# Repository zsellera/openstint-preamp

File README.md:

# OpenStint Loop Preamplifier Board

The **OpenStint Loop Preamplifier Board** is an optional front-end module, designed for the [OpenStint Laptimer System](https://github.com/zsellera/openstint). It provides signal conditioning and amplification for the parallel-wire "antenna", ensuring clean, stable, and maximized signal transfer to the timing receiver.

## 🔧 Features

- Fully compatible with the OpenStint timing receiver interface. Operated from the bias-tee available on HackRF One and RTLSDR.
- Output is matched to 50 Ohm.
- +12 dB gain low-noise amplifier
- Fits Hammond's 1590L-style aluminium cases
- Power pin available for 1S batteries (remove `L6` or `FB2` in this case, or add DC-block capacitor before the SDR).
- Open hardware design – schematics and PCB available under permissive license
- Directly manufacturable at JLCPCB (LCSC part codes provided).

## ✳️ Measurement Results

The following measurements were made at the `VNA_IN` port (after the balun).

**POWER GAIN**

**INPUT MATCHING**

## Schematics

## 🗺 Roadmap / Project ideas

Add an optional 75 Ohm output as well, or add a separate 50 to 50+75 splitter. This hardware change should have a software counterpart, which reads both the OpenStint and MyLaps decoders, and merges the results into a single stream for laptiming applications. We could keep both open and commercial transponders to co-exists on the same track this way. Also, upgrading post-4.4 firmware won't be such a headache neither.

Automatic gain control: even a simple one could increase the dynamic range of the decoders.

---
Part of the OpenStint Laptimer System – open, modular, and precise RC timing.

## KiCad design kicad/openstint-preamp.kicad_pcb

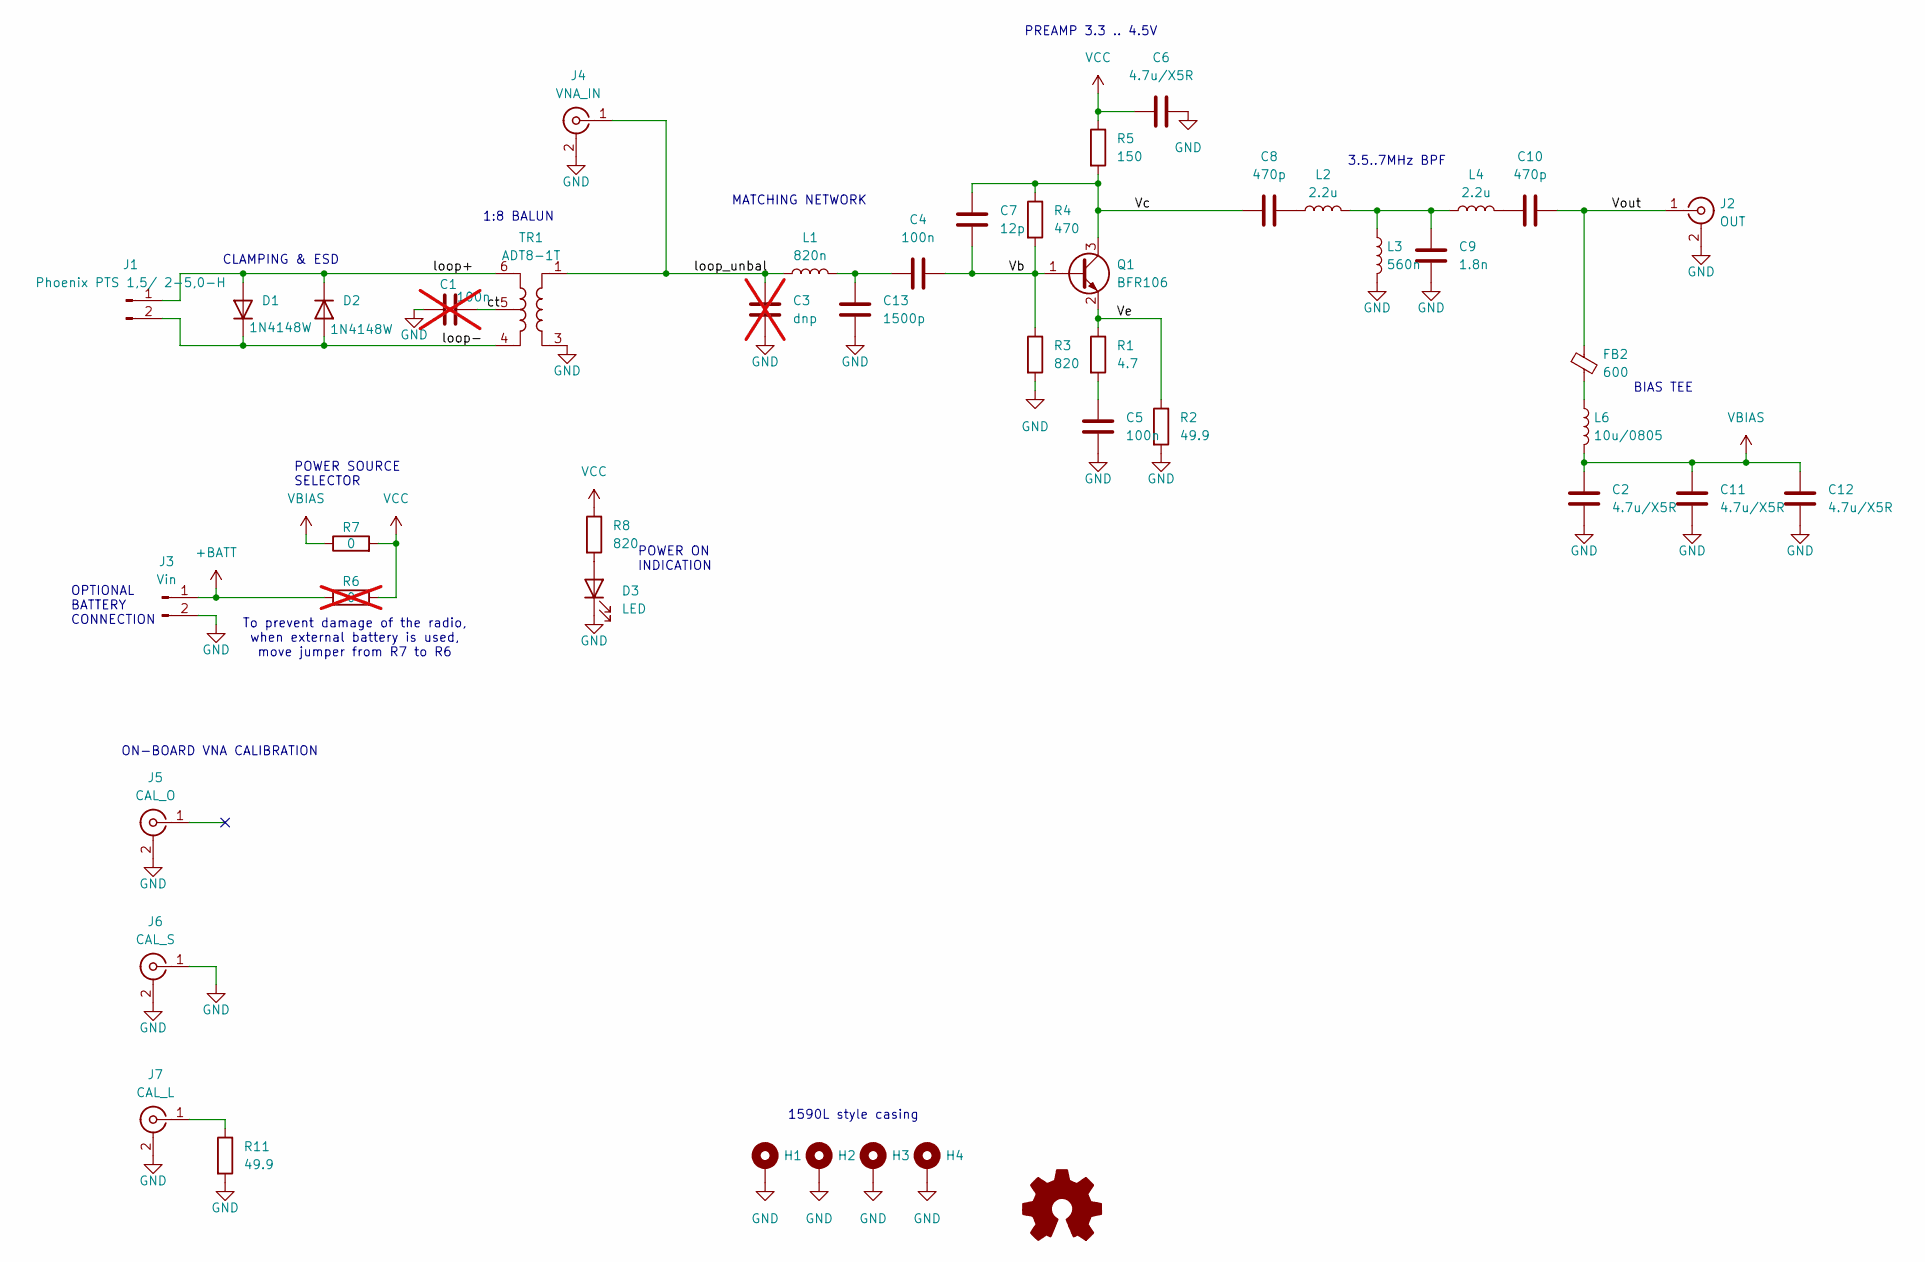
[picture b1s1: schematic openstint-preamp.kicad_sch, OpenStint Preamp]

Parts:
C1: 100n; C_0603_1608Metric; LCSC C14663; not fitted
C2, C6, C11, C12: 4.7u/X5R; C_0603_1608Metric; LCSC C19666
C3: dnp; C_0603_1608Metric; not fitted
C4, C5: 100n; C_0603_1608Metric; LCSC C14663
C7: 12p; C_0603_1608Metric; LCSC C38523
C8, C10: 470p; C_0603_1608Metric; LCSC C1620
C9: 1.8n; C_0603_1608Metric; LCSC C107042
C13: 1500p; C_0603_1608Metric; LCSC C1595
D1, D2: 1N4148W; D_SOD-123F; LCSC C81598
D3: LED; LED_1206_3216Metric_ReverseMount_Hole1.8x2.4mm; mouser 710-156120VS75000
FB2: 600; L_0805_2012Metric; LCSC C1017
H1, H2, H3, H4: MountingHole_Pad; MountingHole_4.3mm_M4_DIN965_Pad
J1: Phoenix PTS 1,5/ 2-5,0-H; TerminalBlock_Phoenix_PT-1,5-2-5.0-H_1x02_P5.00mm_Horizontal; mouser 651-1792863
J2: OUT; SMA_Amphenol_132134-16_Vertical
J3: Vin; JST_PH_B2B-PH-K_1x02_P2.00mm_Vertical; LCSC C131337
J4: VNA_IN; U.FL_Hirose_U.FL-R-SMT-1_Vertical; LCSC C5137195
J5: CAL_O; U.FL_Hirose_U.FL-R-SMT-1_Vertical; LCSC C5137195
J6: CAL_S; U.FL_Hirose_U.FL-R-SMT-1_Vertical; LCSC C5137195
J7: CAL_L; U.FL_Hirose_U.FL-R-SMT-1_Vertical; LCSC C5137195
L1: 820n; L_0603_1608Metric; LCSC C18213078
L2, L4: 2.2u; L_0603_1608Metric; LCSC C337910
L3: 560n; L_0603_1608Metric; LCSC C114773
L6: 10u/0805; L_0805_2012Metric; LCSC C88173
Q1: BFR106; SOT-23; LCSC C439780
R1: 4.7; R_0603_1608Metric; LCSC C23164
R2, R11: 49.9; R_0603_1608Metric; LCSC C23185
R3, R8: 820; R_0603_1608Metric; LCSC C23253
R4: 470; R_0603_1608Metric; LCSC C23179
R5: 150; R_0603_1608Metric; LCSC C22808
R6: 0; R_0603_1608Metric; LCSC C21189; not fitted
R7: 0; R_0603_1608Metric; LCSC C21189
SYM1: Logo_Open_Hardware_Small; OSHW-Logo2_9.8x8mm_SilkScreen
TR1: ADT8-1T; Mini-Circuits_CD637_H5.23mm

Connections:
+BATT: J3.1, R6.1
/Vb: C4.2, C7.1, Q1.1 (B), R3.1, R4.2
/Vc: C7.2, C8.1, Q1.3 (C), R4.1, R5.2
/Ve: Q1.2 (E), R1.1, R2.1
/Vout: C10.2, FB2.1, J2.1 (In)
/ct: C1.2, TR1.5
/loop+: D1.2 (A), D2.1 (K), J1.1, TR1.6
/loop-: D1.1 (K), D2.2 (A), J1.2, TR1.4
/loop_unbal: C3.1, J4.1 (In), L1.1, TR1.1
GND: C1.1, C2.1, C3.2, C5.2, C6.2, C9.2, C11.1, C12.1, C13.2, D3.1 (K), H1.1, H2.1, H3.1, H4.1, J2.2 (Ext), J3.2, J4.2 (Ext), J5.2 (Ext), J6.1 (In), J6.2 (Ext), J7.2 (Ext), L3.2, R2.2, R3.2, R11.2, TR1.3
unnamed: C5.1, R1.2
unnamed: C8.2, L2.1
unnamed: C9.1, L2.2, L3.1, L4.1
unnamed: C10.1, L4.2
unnamed: C4.1, C13.1, L1.2
unnamed: D3.2 (A), R8.2
unnamed: FB2.2, L6.1
unnamed: J7.1 (In), R11.1
VBIAS: C2.2, C11.2, C12.2, L6.2, R7.1
VCC: C6.1, R5.1, R6.2, R7.2, R8.1

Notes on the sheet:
POWER ON INDICATION
MATCHING NETWORK
OPTIONAL BATTERY CONNECTION
BIAS TEE
1590L style casing
ON-BOARD VNA CALIBRATION
PREAMP 3.3 .. 4.5V
1:8 BALUN
POWER SOURCE SELECTOR
CLAMPING & ESD
To prevent damage of the radio, when external battery is used, move jumper from R7 to R6
3.5..7MHz BPF

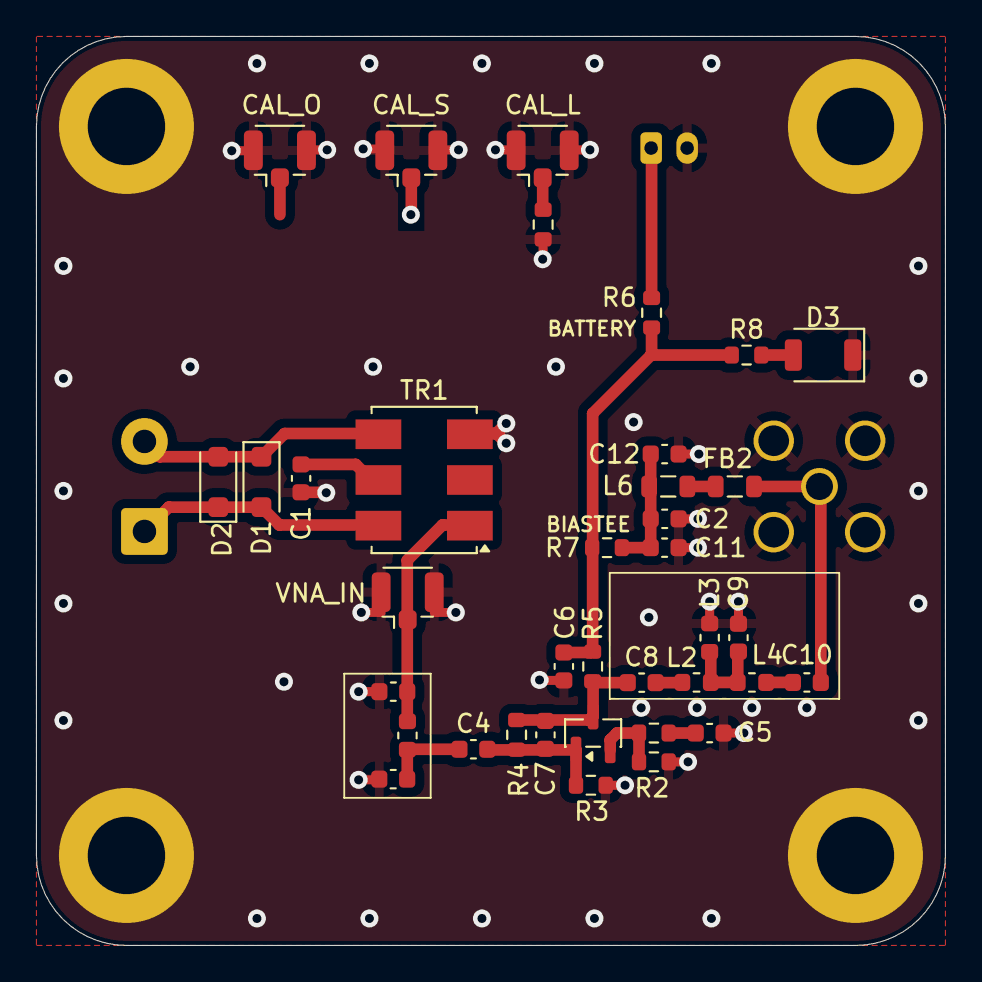
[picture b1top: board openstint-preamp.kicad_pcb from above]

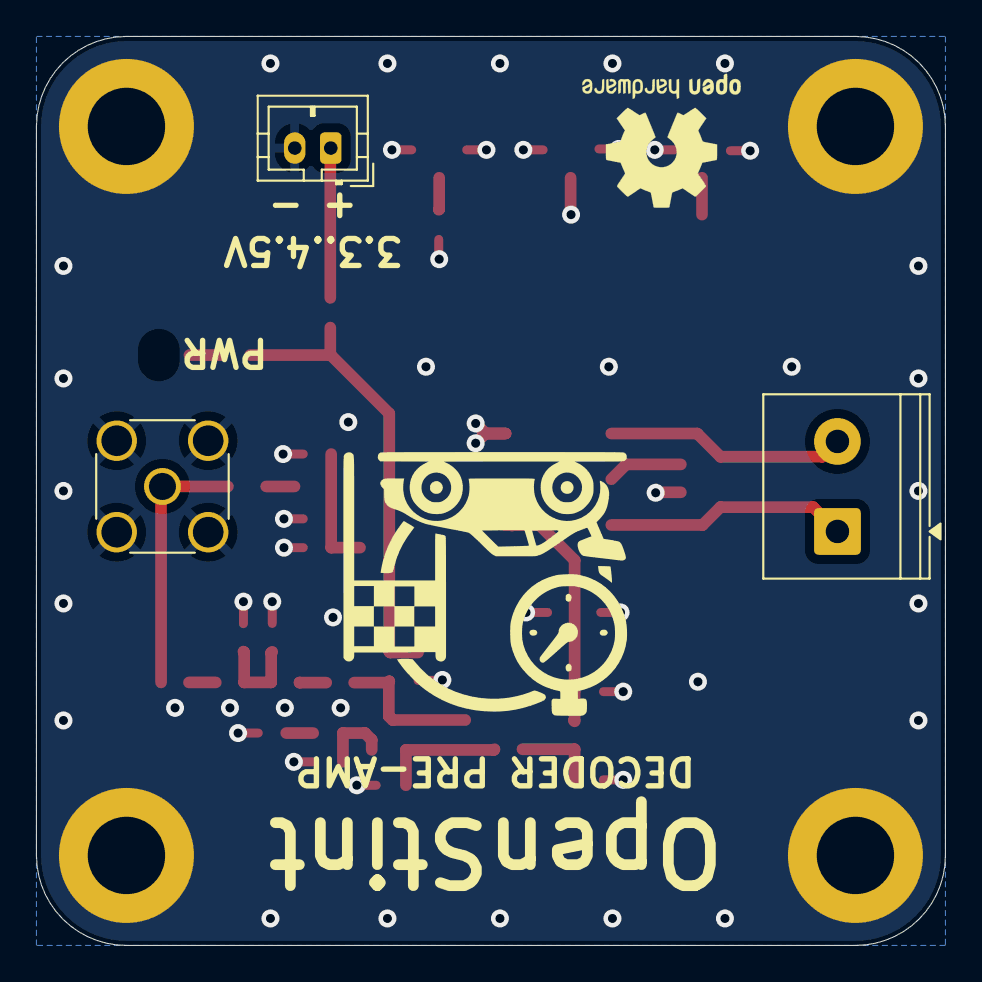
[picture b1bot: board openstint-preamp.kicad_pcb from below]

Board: 2 copper layers, 50.5 x 50.5 mm, 45 parts (4 on the bottom side), 20 nets.

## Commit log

2025-11-07 readme added
2025-11-07 Fix GitHub link and add schematics section
    Updated the GitHub link in the README and added a schematics section with an image.
2025-11-08 added roadmap section to readme
2025-11-11 add image
2025-12-07 Add measurement results to readme
2025-12-08 matching network, battery connection, oshw logo
2026-06-22 github action
2026-06-22 gh actions: panelize
